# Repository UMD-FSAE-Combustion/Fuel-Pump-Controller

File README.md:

# Fuel-Pump-Controller
PCB Design for the Fuel Pump Motor Controller

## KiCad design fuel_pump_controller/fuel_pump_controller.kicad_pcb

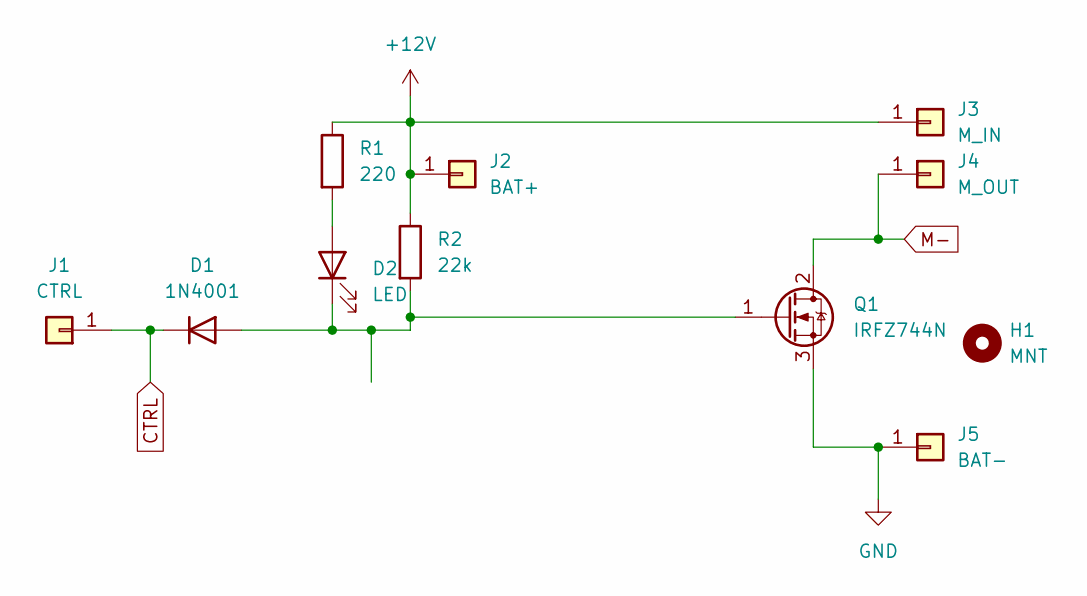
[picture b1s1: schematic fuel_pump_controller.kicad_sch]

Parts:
D1: 1N4001; D_DO-41_SOD81_P10.16mm_Horizontal
D2: LED; LED_D5.0mm
H1: MNT; MountingHole_2.1mm
J1: CTRL; Pin_D1.0mm_L10.0mm
J2: BAT+; Pin_D1.4mm_L8.5mm_W2.8mm_FlatFork
J3: M_IN; SolderWire-1sqmm_1x01_D1.4mm_OD2.7mm
J4: M_OUT; SolderWire-1sqmm_1x01_D1.4mm_OD2.7mm
J5: BAT-; SolderWire-1sqmm_1x01_D1.4mm_OD2.7mm
Q1: IRFZ744N; TO-220-3_JB
R1: 220; R_Axial_DIN0204_L3.6mm_D1.6mm_P5.08mm_Horizontal
R2: 22k; R_Axial_DIN0204_L3.6mm_D1.6mm_P5.08mm_Horizontal

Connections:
+12V: J2.1, J3.1, R1.1, R2.1
CTRL: D1.1 (K), J1.1
GND: J5.1, Q1.3 (S)
M-: J4.1, Q1.2 (D)
unnamed: D1.2 (A), D2.1 (K), Q1.1 (G), R2.2
unnamed: D2.2 (A), R1.2

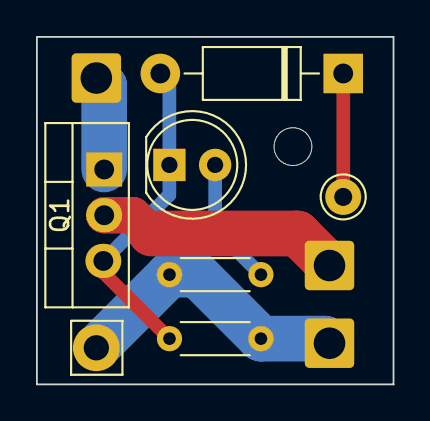
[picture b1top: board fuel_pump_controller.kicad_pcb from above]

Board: 2 copper layers, 19.8 x 19.3 mm, 11 parts (0 on the bottom side), 6 nets.

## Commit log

2023-02-08 Added files for the first iteration without DRC errors
2023-02-08 Moved some files around
